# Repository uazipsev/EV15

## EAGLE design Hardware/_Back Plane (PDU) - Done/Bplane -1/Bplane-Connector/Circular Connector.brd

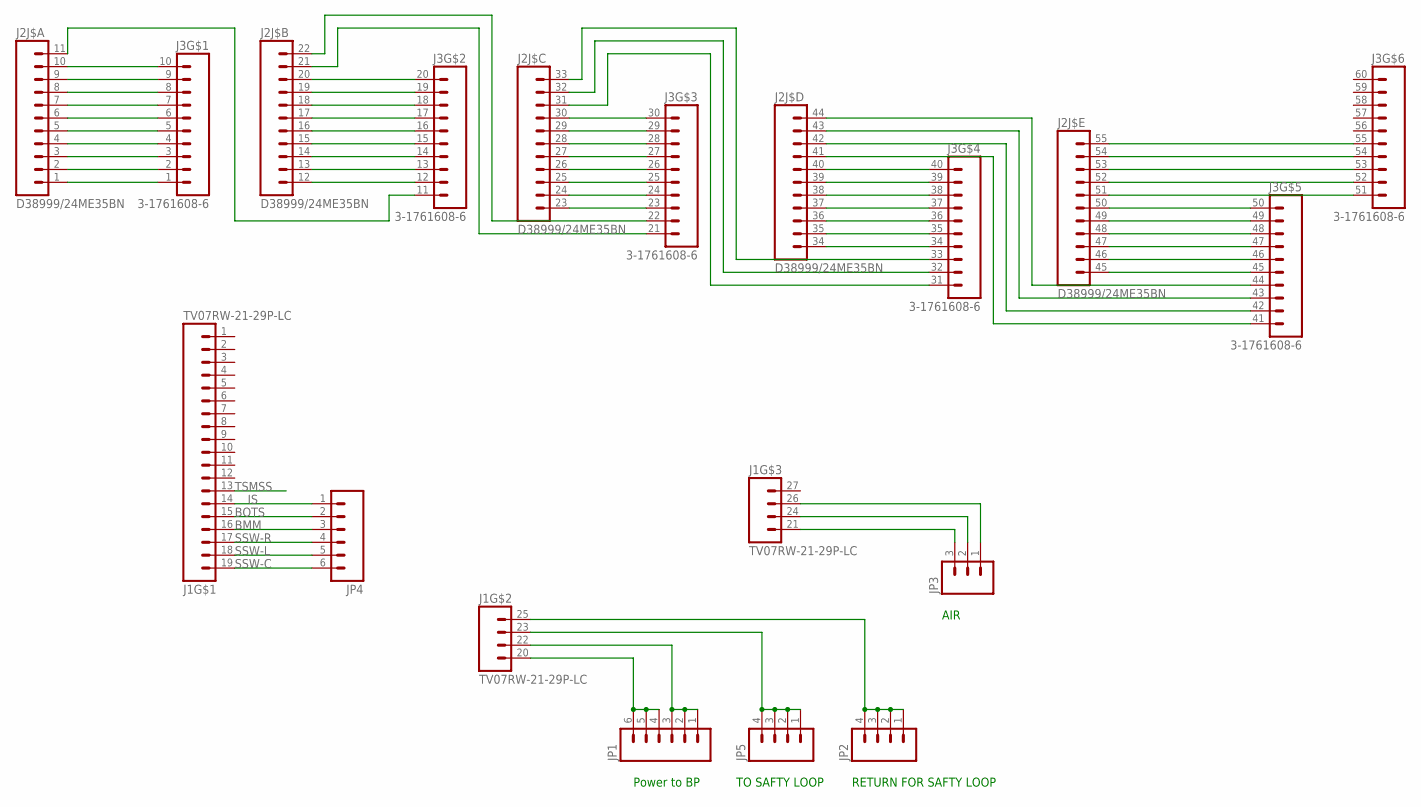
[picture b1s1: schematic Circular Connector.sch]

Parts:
J1: TV07RW-21-29P-LC
J2: D38999/24ME35BN
J3: 3-1761608-6
JP1, JP4: M06POLAR_LOCK; MOLEX-1X6_LOCK
JP2, JP5: M04POLAR_LOCK; MOLEX-1X4_LOCK
JP3: M03POLAR_LOCK; MOLEX-1X3_LOCK

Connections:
BMM: JP4.3
BOTS: JP4.2
IS: J1.14, JP4.1
unnamed: J2.1, J3.1
unnamed: J2.2, J3.2
unnamed: J2.3, J3.3
unnamed: J2.4, J3.4
unnamed: J2.5, J3.5
unnamed: J2.6, J3.6
unnamed: J2.7, J3.7
unnamed: J2.8, J3.8
unnamed: J2.9, J3.9
unnamed: J2.10, J3.10
unnamed: J2.11, J3.11 (1)
unnamed: J2.12 (1), J3.12 (2)
unnamed: J2.13 (2), J3.13 (3)
unnamed: J2.14 (3), J3.14 (4)
unnamed: J2.15 (4), J3.15 (5)
unnamed: J2.16 (5), J3.16 (6)
unnamed: J2.17 (6), J3.17 (7)
unnamed: J2.18 (7), J3.18 (8)
unnamed: J2.19 (8), J3.19 (9)
unnamed: J2.20 (9), J3.20 (10)
unnamed: J2.21 (10), J3.21 (1)
unnamed: J2.22 (11), J3.22 (2)
unnamed: J2.23 (1), J3.23 (3)
unnamed: J2.24 (2), J3.24 (4)
unnamed: J2.25 (3), J3.25 (5)
unnamed: J2.26 (4), J3.26 (6)
unnamed: J2.27 (5), J3.27 (7)
unnamed: J2.28 (6), J3.28 (8)
unnamed: J2.29 (7), J3.29 (9)
unnamed: J2.30 (8), J3.30 (10)
unnamed: J2.31 (9), J3.31 (1)
unnamed: J2.32 (10), J3.32 (2)
unnamed: J2.33 (11), J3.33 (3)
unnamed: J2.34 (1), J3.34 (4)
unnamed: J2.35 (2), J3.35 (5)
unnamed: J2.36 (3), J3.36 (6)
unnamed: J2.37 (4), J3.37 (7)
unnamed: J2.38 (5), J3.38 (8)
unnamed: J2.39 (6), J3.39 (9)
unnamed: J2.40 (7), J3.40 (10)
unnamed: J2.41 (8), J3.41 (1)
unnamed: J2.42 (9), J3.42 (2)
unnamed: J2.43 (10), J3.43 (3)
unnamed: J2.44 (11), J3.44 (4)
unnamed: J2.45 (1), J3.45 (5)
unnamed: J2.46 (2), J3.46 (6)
unnamed: J2.47 (3), J3.47 (7)
unnamed: J2.48 (4), J3.48 (8)
unnamed: J2.49 (5), J3.49 (9)
unnamed: J2.50 (6), J3.50 (10)
unnamed: J2.51 (7), J3.51 (1)
unnamed: J2.52 (8), J3.52 (2)
unnamed: J2.53 (9), J3.53 (3)
unnamed: J2.54 (10), J3.54 (4)
unnamed: J2.55 (11), J3.55 (5)
unnamed: J1.20 (1), JP1.4, JP1.5, JP1.6
unnamed: J1.22 (2), JP1.1, JP1.2, JP1.3
unnamed: J1.25 (4), JP2.1, JP2.2, JP2.3, JP2.4
unnamed: J1.21 (1), JP3.3
unnamed: J1.24 (2), JP3.2
unnamed: J1.26 (3), JP3.1
unnamed: J1.23 (3), JP5.1, JP5.2, JP5.3, JP5.4
SSW-C: J1.19, JP4.6
SSW-L: JP4.5
SSW-R: JP4.4
TSMSS: J1.13

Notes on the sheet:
Power to BP
RETURN FOR SAFTY LOOP
AIR
TO SAFTY LOOP

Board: 2 copper layers, 8 parts (3 on the bottom side), 64 nets, no tracks yet.

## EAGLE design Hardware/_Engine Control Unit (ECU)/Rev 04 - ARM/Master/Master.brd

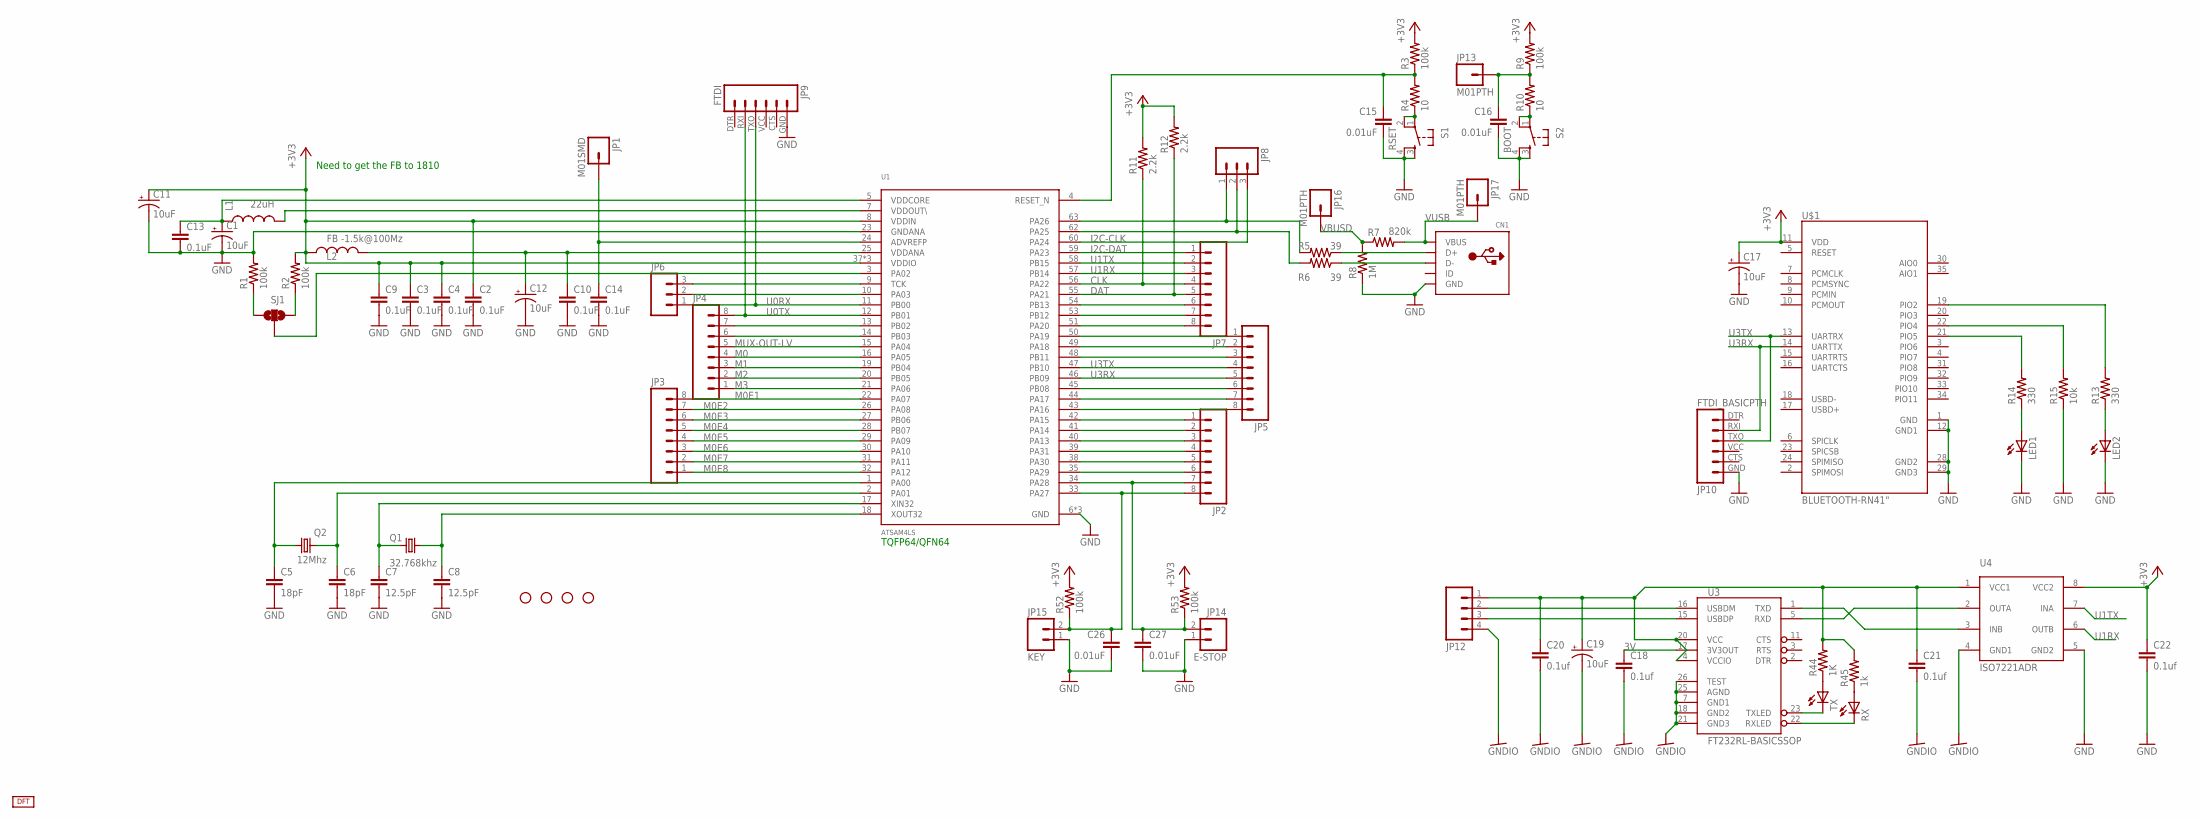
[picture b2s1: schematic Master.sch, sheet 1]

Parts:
C1, C11, C12, C17, C19: 10uF; EIA3216
C2, C3, C4, C9, C10, C13, C14: 0.1uF; 0805
C5, C6: 18pF; 0805
C7, C8: 12.5pF; 0805
C15, C16, C26, C27: 0.01uF; 0805
C18, C20, C21, C22: 0.1uf; 0805
CN1: USBMOLEX; USB-MINIB-THM-MOLEX
JP1: M01SMD; LUXEON-PAD
JP2, JP3, JP4, JP5, JP7: M08LOCK; 1X08_LOCK
JP6, JP8: M03LOCK; 1X03_LOCK
JP9: FTDI; FTDI_BASIC
JP10: FTDI_BASICPTH; FTDI_BASIC
JP12: M04POLAR_LOCK; MOLEX-1X4_LOCK
JP13, JP16, JP17: M01PTH; 1X01
JP14: E-STOP; 1X02_LOCK
JP15: KEY; 1X02_LOCK
L1: 22uH; 0805
L2: FB -1.5k@100Mz; 0805
LED1, LED2: LEDCHIP-LED0805; CHIP-LED0805
Q1: 32.768khz; MM20SS
Q2: 12Mhz; CTS406
R1, R2, R3, R9, R52, R53: 100k; 0805
R4, R10: 10; 0805
R5, R6: 39; 0805
R7: 820k; 0805
R8: 1M; 0805
R11, R12: 2.2k; 0805
R13, R14: 330; 0805
R15: 10k; 0805
R44: 1K; R0805
R45: 1k; R0805
RX: LEDCHIPLED_0805; CHIPLED_0805
S1: RSET; TACTILE-PTH
S2: BOOT; TACTILE-PTH
SJ1: SOLDERJUMPER_2WAYS; SJ_3
STANDOFF1, STANDOFF2, STANDOFF3, STANDOFF4: STAND-OFF
TX: LEDCHIPLED_0805; CHIPLED_0805
U1: ATSAM4LS; TQFP-64
U3: FT232RL-BASICSSOP; SSOP28DB
U4: ISO7221ADR; SOIC-8
U$1: BLUETOOTH-RN41"; RN41
U$12: LOGO; LOGO-S

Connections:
3V: C18.1, U3.17 (3V3OUT)
+3V3: C2.1, C3.1, C4.1, C9.1, C11.A (+), C17.A (+), C22.1, L2.1, R2.2, R3.2, R9.2, R11.2, R12.2, R52.2, R53.2, U1.8 (VDDIN), U1.37 (VDDIO), U1.52 (VDDIO), U1.61 (VDDIO), U4.8 (VCC2), U$1.11 (VDD); also elsewhere on the board
CLK: JP7.4, R11.1, U1.56 (PA22)
DAT: JP7.5, R12.1, U1.55 (PA21)
GND: C1.C (-), C2.2, C3.2, C4.2, C5.2, C6.2, C7.2, C8.2, C9.2, C10.2, C11.C (-), C12.C (-), C13.2, C14.2, C15.2, C16.2, C17.C (-), C22.2, C26.2, C27.2, CN1.GND, JP9.GND (6), JP10.GND (6), JP14.1, JP15.1, LED1.C, LED2.C, R1.2, R8.1, R15.1, S1.3, S1.4, S2.3, S2.4, U1.6 (GND), U1.23 (GNDANA), U1.36 (GND), U1.64 (GND), U4.5 (GND2), U$1.1 (GND), U$1.12 (GND1), U$1.28 (GND2), U$1.29 (GND3); also elsewhere on the board
GNDIO: C18.2, C19.C (-), C20.2, C21.2, JP12.4, U3.7 (GND1), U3.18 (GND2), U3.21 (GND3), U3.25 (AGND), U3.26 (TEST), U4.4 (GND1)
I2C-CLK: JP8.3, U1.60 (PA24); also elsewhere on the board
I2C-DAT: JP7.1, U1.59 (PA23); also elsewhere on the board
M0: JP4.4, U1.16 (PA05); also elsewhere on the board
M0E1: JP3.8, U1.22 (PA07); also elsewhere on the board
M0E2: JP3.7, U1.26 (PA08); also elsewhere on the board
M0E3: JP3.6, U1.27 (PB06); also elsewhere on the board
M0E4: JP3.5, U1.28 (PB07); also elsewhere on the board
M0E5: JP3.4, U1.29 (PA09); also elsewhere on the board
M0E6: JP3.3, U1.30 (PA10); also elsewhere on the board
M0E7: JP3.2, U1.31 (PA11); also elsewhere on the board
M0E8: JP3.1, U1.32 (PA12); also elsewhere on the board
M1: JP4.3, U1.19 (PB04); also elsewhere on the board
M2: JP4.2, U1.20 (PB05); also elsewhere on the board
M3: JP4.1, U1.21 (PA06); also elsewhere on the board
MUX-OUT-LV: JP4.5, U1.15 (PA04); also elsewhere on the board
unnamed: R4.1, S1.1, S1.2
unnamed: L1.2, U1.7 (VDDOUT\)
unnamed: C1.A (+), C13.1, L1.1, U1.5 (VDDCORE)
unnamed: C7.1, Q1.1, U1.17 (XIN32)
unnamed: SJ1.2, U1.3 (PA02)
unnamed: C8.1, Q1.4 (2), U1.18 (XOUT32)
unnamed: R1.1, SJ1.3
unnamed: C6.1, Q2.1, U1.2 (PA01)
unnamed: C5.1, Q2.3 (2), U1.1 (PA00)
unnamed: R2.1, SJ1.1
unnamed: C10.1, C12.A (+), L2.2, U1.25 (VDDANA)
unnamed: C14.1, JP1.P$1, U1.24 (ADVREFP)
unnamed: C15.1, R3.1, R4.2, U1.4 (RESET_N)
unnamed: R10.1, S2.1, S2.2
unnamed: CN1.D+, R5.1
unnamed: CN1.D-, R6.1
unnamed: C16.1, JP13.1, R9.1, R10.2
unnamed: JP8.1, R5.2, U1.63 (PA26)
unnamed: JP8.2, R6.2, U1.62 (PA25)
unnamed: LED2.A, R13.1
unnamed: JP2.1, U1.42 (PA15)
unnamed: JP2.2, U1.41 (PA14)
unnamed: JP2.3, U1.40 (PA13)
unnamed: JP2.4, U1.39 (PA31)
unnamed: JP2.5, U1.38 (PA30)
unnamed: JP2.6, U1.35 (PA29)
unnamed: C26.1, JP2.8, JP15.2, R52.1, U1.33 (PA27)
unnamed: C27.1, JP2.7, JP14.2, R53.1, U1.34 (PA28)
unnamed: C19.A (+), C20.1, C21.1, JP12.1, R44.2, R45.2, U3.4 (VCCIO), U3.20 (VCC), U4.1 (VCC1)
unnamed: JP12.2, U3.16 (USBDM)
unnamed: JP12.3, U3.15 (USBDP)
unnamed: R44.1, TX.A
unnamed: JP4.6, U1.14 (PB03)
unnamed: JP4.7, U1.13 (PB02)
unnamed: JP5.8, U1.43 (PA16)
unnamed: JP5.7, U1.44 (PA17)
unnamed: JP5.6, U1.45 (PB08)
unnamed: JP5.3, U1.48 (PB11)
unnamed: JP5.2, U1.49 (PA18)
unnamed: JP5.1, U1.50 (PA19)
unnamed: JP6.2, U1.10 (PA03)
unnamed: JP6.3, U1.9 (TCK)
unnamed: JP7.8, U1.51 (PA20)
unnamed: JP7.7, U1.53 (PB12)
unnamed: JP7.6, U1.54 (PB13)
unnamed: LED1.A, R14.1
unnamed: R14.2, U$1.21 (PIO5)
unnamed: R13.2, U$1.19 (PIO2)
unnamed: R45.1, RX.A
unnamed: R15.2, U$1.22 (PIO4)
unnamed: TX.C, U3.23 (TXLED)
unnamed: RX.C, U3.22 (RXLED)
unnamed: U3.1 (TXD), U4.3 (INB)
unnamed: U3.5 (RXD), U4.2 (OUTA)
U0RX: JP6.1, JP9.TXO (3), U1.11 (PB00)
U0TX: JP4.8, JP9.RXI (2), U1.12 (PB01)
U1RX: JP7.3, U1.57 (PB14), U4.6 (OUTB)
U1TX: JP7.2, U1.58 (PB15), U4.7 (INA)
U3RX: JP5.5, JP10.RXI (2), U1.46 (PB09), U$1.14 (UARTTX)
U3TX: JP5.4, JP10.TXO (3), U1.47 (PB10), U$1.13 (UARTRX)
VBUSD: JP16.1, R7.1, R8.2
VUSB: CN1.VBUS, JP17.1, R7.2

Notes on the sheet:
TQFP64/QFN64
Need to get the FB to 1810

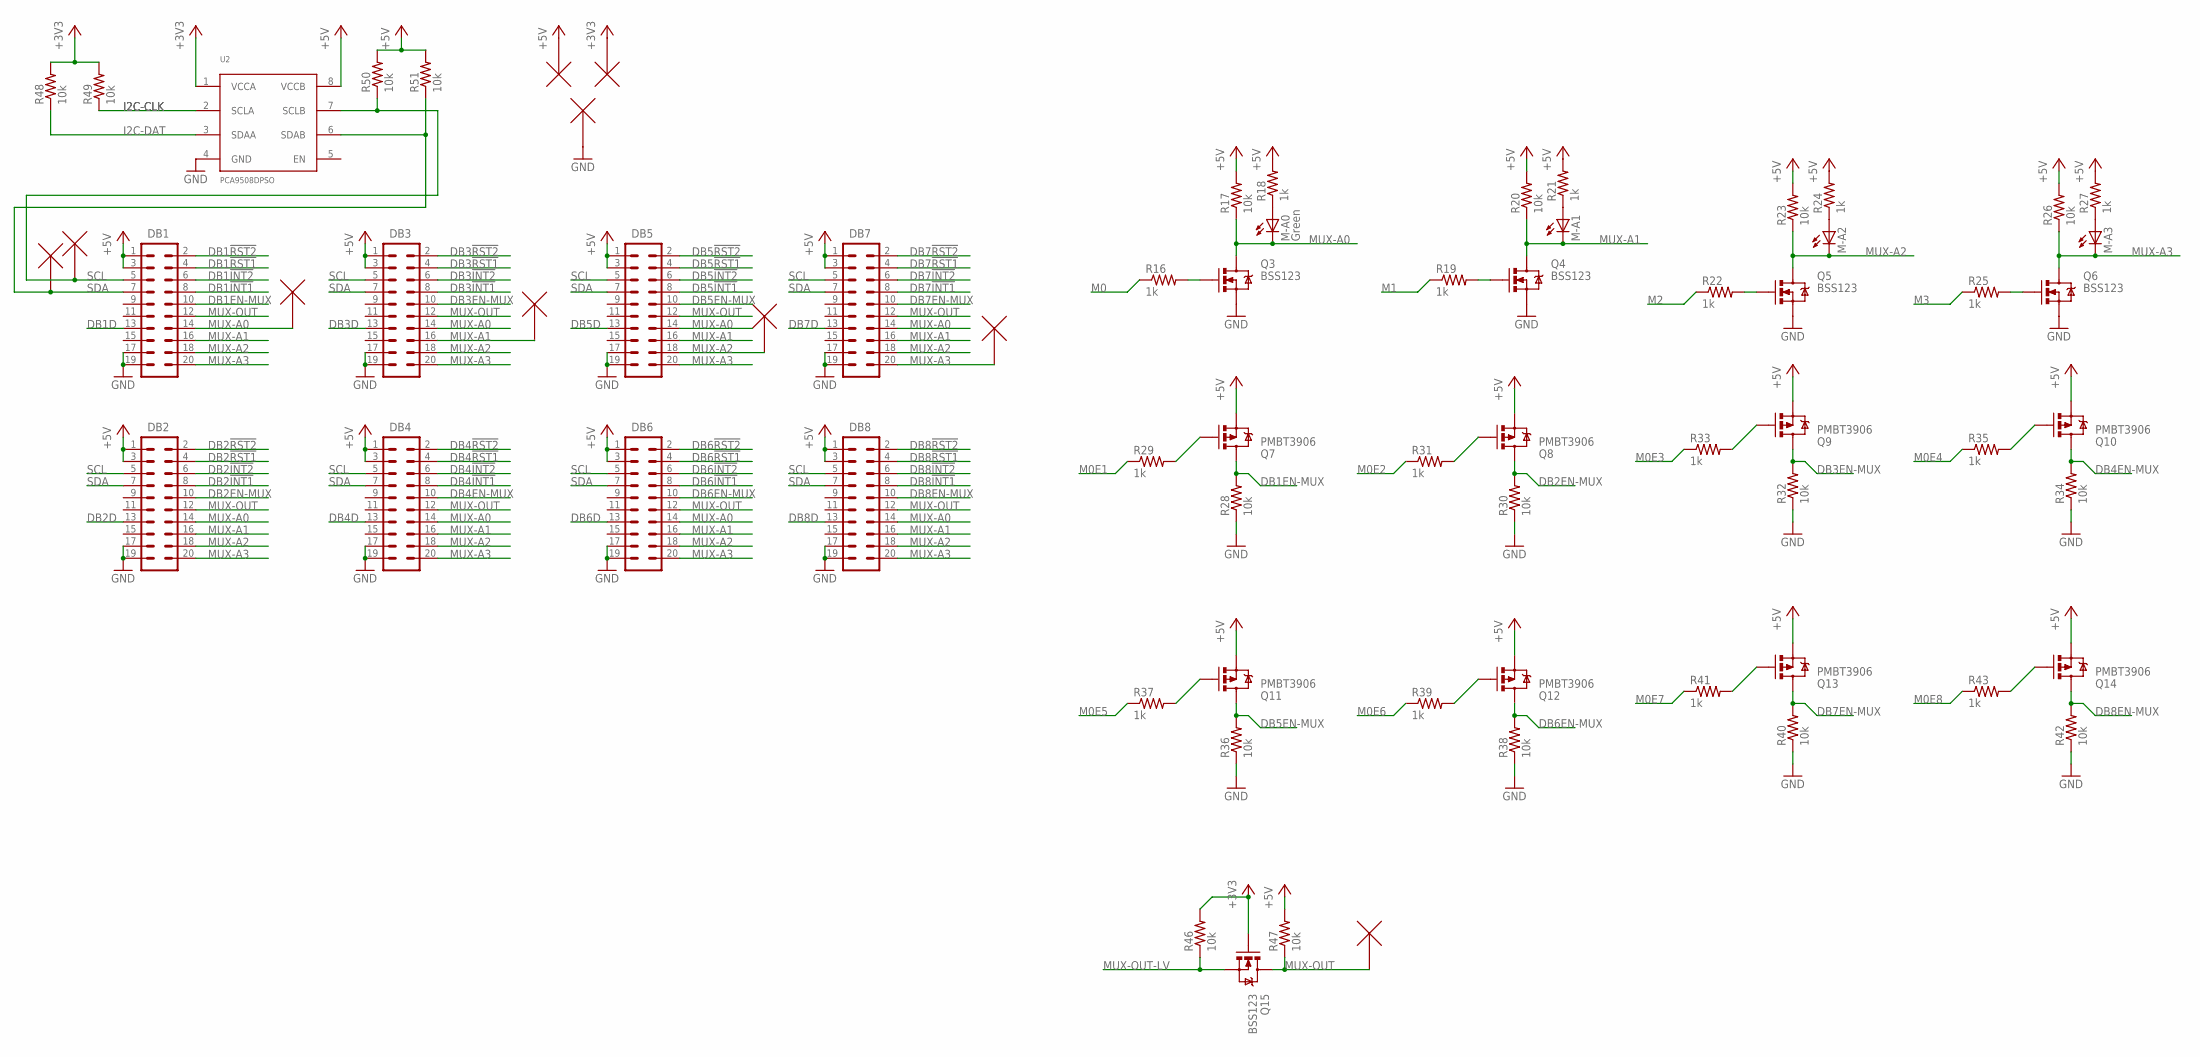
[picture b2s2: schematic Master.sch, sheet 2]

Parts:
DB1, DB2, DB3, DB4, DB5, DB6, DB7, DB8: M10X2SPECIAL; 2X10_LOCK_SPECIAL
M-A0: Green; CHIP-LED0805
M-A1, M-A2, M-A3: LEDCHIP-LED0805; CHIP-LED0805
Q3, Q4, Q5, Q6, Q15: BSS123; SOT23
Q7, Q8, Q9, Q10, Q11, Q12, Q13, Q14: PMBT3906; SOT23-3
R16, R18, R19, R21, R22, R24, R25, R27, R29, R31, R33, R35, R37, R39, R41, R43: 1k; 0805
R17, R20, R23, R26, R28, R30, R32, R34, R36, R38, R40, R42, R46, R47, R48, R49, R50, R51: 10k; 0805
U2: PCA9508DPSO; SO-8
U$2, U$3, U$4, U$5, U$6, U$7, U$8, U$9, U$10, U$13: TESTPOINT; R0603

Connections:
+3V3: Q15.1 (G), R46.2, R48.2, R49.2, U2.1 (VCCA), U$9.1, U$9.2; also elsewhere on the board
+5V: DB1.1, DB1.3, DB2.1, DB2.3, DB3.1, DB3.3, DB4.1, DB4.3, DB5.1, DB5.3, DB6.1, DB6.3, DB7.1, DB7.3, DB8.1, DB8.3, Q7.2 (S), Q8.2 (S), Q9.2 (S), Q10.2 (S), Q11.2 (S), Q12.2 (S), Q13.2 (S), Q14.2 (S), R17.2, R18.2, R20.2, R21.2, R23.2, R24.2, R26.2, R27.2, R47.2, R50.2, R51.2, U2.8 (VCCB), U$8.1, U$8.2; also elsewhere on the board
DB1!INT1: DB1.8
DB1!INT2: DB1.6
DB1!RST1: DB1.4
DB1!RST2: DB1.2
DB1D: DB1.13
DB1EN-MUX: DB1.10, Q7.3 (D), R28.2
DB2!INT1: DB2.8
DB2!INT2: DB2.6
DB2!RST1: DB2.4
DB2!RST2: DB2.2
DB2D: DB2.13
DB2EN-MUX: DB2.10, Q8.3 (D), R30.2
DB3!INT1: DB3.8
DB3!INT2: DB3.6
DB3!RST1: DB3.4
DB3!RST2: DB3.2
DB3D: DB3.13
DB3EN-MUX: DB3.10, Q9.3 (D), R32.2
DB4!INT1: DB4.8
DB4!INT2: DB4.6
DB4!RST1: DB4.4
DB4!RST2: DB4.2
DB4D: DB4.13
DB4EN-MUX: DB4.10, Q10.3 (D), R34.2
DB5!INT1: DB5.8
DB5!INT2: DB5.6
DB5!RST1: DB5.4
DB5!RST2: DB5.2
DB5D: DB5.13
DB5EN-MUX: DB5.10, Q11.3 (D), R36.2
DB6!INT1: DB6.8
DB6!INT2: DB6.6
DB6!RST1: DB6.4
DB6!RST2: DB6.2
DB6D: DB6.13
DB6EN-MUX: DB6.10, Q12.3 (D), R38.2
DB7!INT1: DB7.8
DB7!INT2: DB7.6
DB7!RST1: DB7.4
DB7!RST2: DB7.2
DB7D: DB7.13
DB7EN-MUX: DB7.10, Q13.3 (D), R40.2
DB8!INT1: DB8.8
DB8!INT2: DB8.6
DB8!RST1: DB8.4
DB8!RST2: DB8.2
DB8D: DB8.13
DB8EN-MUX: DB8.10, Q14.3 (D), R42.2
GND: DB1.17, DB1.19, DB2.17, DB2.19, DB3.17, DB3.19, DB4.17, DB4.19, DB5.17, DB5.19, DB6.17, DB6.19, DB7.17, DB7.19, DB8.17, DB8.19, Q3.2 (S), Q4.2 (S), Q5.2 (S), Q6.2 (S), R28.1, R30.1, R32.1, R34.1, R36.1, R38.1, R40.1, R42.1, U2.4 (GND), U$10.1, U$10.2; also elsewhere on the board
I2C-CLK: R49.1, U2.2 (SCLA); also elsewhere on the board
I2C-DAT: R48.1, U2.3 (SDAA); also elsewhere on the board
M0: R16.1; also elsewhere on the board
M0E1: R29.1; also elsewhere on the board
M0E2: R31.1; also elsewhere on the board
M0E3: R33.1; also elsewhere on the board
M0E4: R35.1; also elsewhere on the board
M0E5: R37.1; also elsewhere on the board
M0E6: R39.1; also elsewhere on the board
M0E7: R41.1; also elsewhere on the board
M0E8: R43.1; also elsewhere on the board
M1: R19.1; also elsewhere on the board
M2: R22.1; also elsewhere on the board
M3: R25.1; also elsewhere on the board
MUX-A0: DB1.14, DB2.14, DB3.14, DB4.14, DB5.14, DB6.14, DB7.14, DB8.14, M-A0.C, Q3.3 (D), R17.1, U$4.1, U$4.2
MUX-A1: DB1.16, DB2.16, DB3.16, DB4.16, DB5.16, DB6.16, DB7.16, DB8.16, M-A1.C, Q4.3 (D), R20.1, U$5.1, U$5.2
MUX-A2: DB1.18, DB2.18, DB3.18, DB4.18, DB5.18, DB6.18, DB7.18, DB8.18, M-A2.C, Q5.3 (D), R23.1, U$6.1, U$6.2
MUX-A3: DB1.20, DB2.20, DB3.20, DB4.20, DB5.20, DB6.20, DB7.20, DB8.20, M-A3.C, Q6.3 (D), R26.1, U$7.1, U$7.2
MUX-OUT: DB1.12, DB2.12, DB3.12, DB4.12, DB5.12, DB6.12, DB7.12, DB8.12, Q15.3 (D), R47.1, U$13.1, U$13.2
MUX-OUT-LV: Q15.2 (S), R46.1; also elsewhere on the board
unnamed: Q3.1 (G), R16.2
unnamed: M-A0.A, R18.1
unnamed: Q4.1 (G), R19.2
unnamed: M-A1.A, R21.1
unnamed: Q5.1 (G), R22.2
unnamed: M-A2.A, R24.1
unnamed: Q6.1 (G), R25.2
unnamed: M-A3.A, R27.1
unnamed: Q8.1 (G), R31.2
unnamed: Q7.1 (G), R29.2
unnamed: Q9.1 (G), R33.2
unnamed: Q10.1 (G), R35.2
unnamed: Q11.1 (G), R37.2
unnamed: Q12.1 (G), R39.2
unnamed: Q13.1 (G), R41.2
unnamed: Q14.1 (G), R43.2
SCL: DB1.5, DB2.5, DB3.5, DB4.5, DB5.5, DB6.5, DB7.5, DB8.5, R50.1, U2.7 (SCLB), U$2.1, U$2.2
SDA: DB1.7, DB2.7, DB3.7, DB4.7, DB5.7, DB6.7, DB7.7, DB8.7, R51.1, U2.6 (SDAB), U$3.1, U$3.2

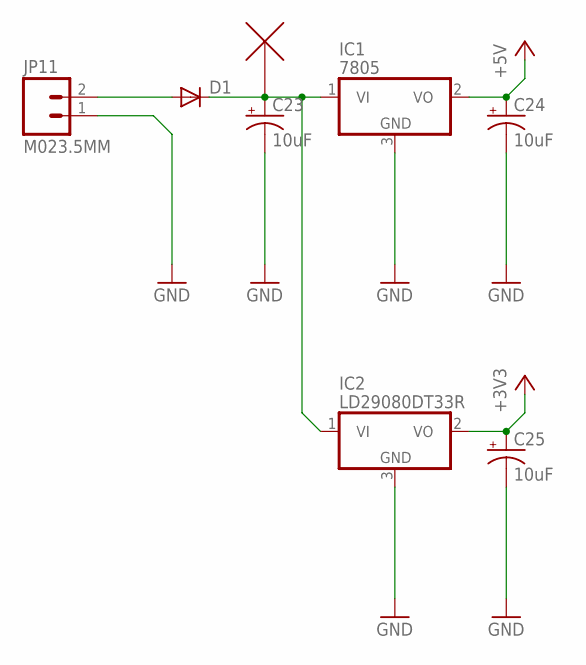
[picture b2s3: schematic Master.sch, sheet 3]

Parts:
C23: 10uF; EIA6032
C24, C25: 10uF; EIA3216
D1: DIODESMA; SMA-DIODE
IC1: 7805; TO252
IC2: LD29080DT33R; TO252
JP11: M023.5MM; SCREWTERMINAL-3.5MM-2
U$11: TESTPOINT; R0603

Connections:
+3V3: C25.A (+), IC2.2 (VO); also elsewhere on the board
+5V: C24.A (+), IC1.2 (VO); also elsewhere on the board
GND: C23.P$2 (-), C24.C (-), C25.C (-), IC1.3 (GND), IC2.3 (GND), JP11.1; also elsewhere on the board
unnamed: C23.P$1 (+), D1.C, IC1.1 (VI), IC2.1 (VI), U$11.1, U$11.2
unnamed: D1.A, JP11.2

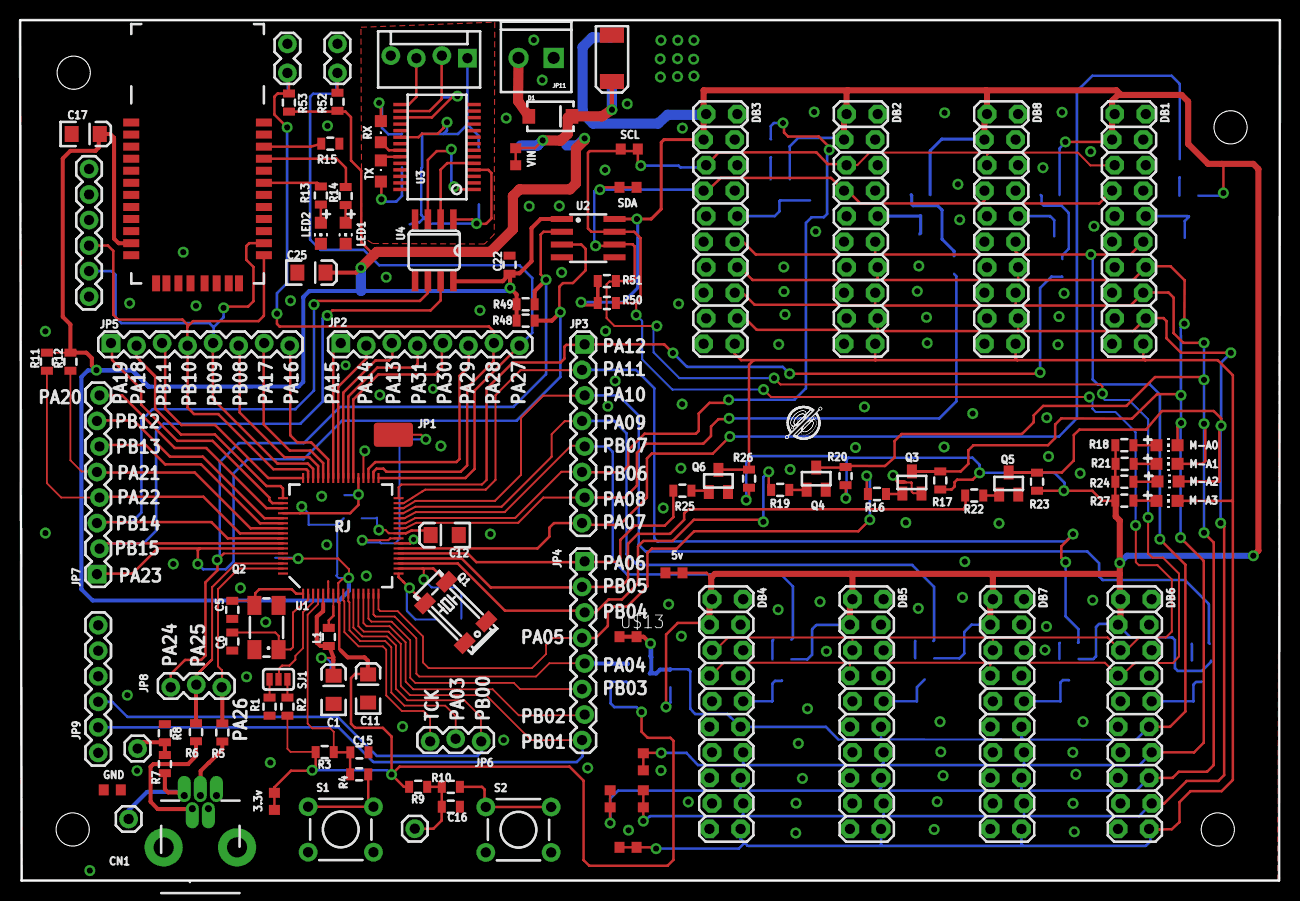
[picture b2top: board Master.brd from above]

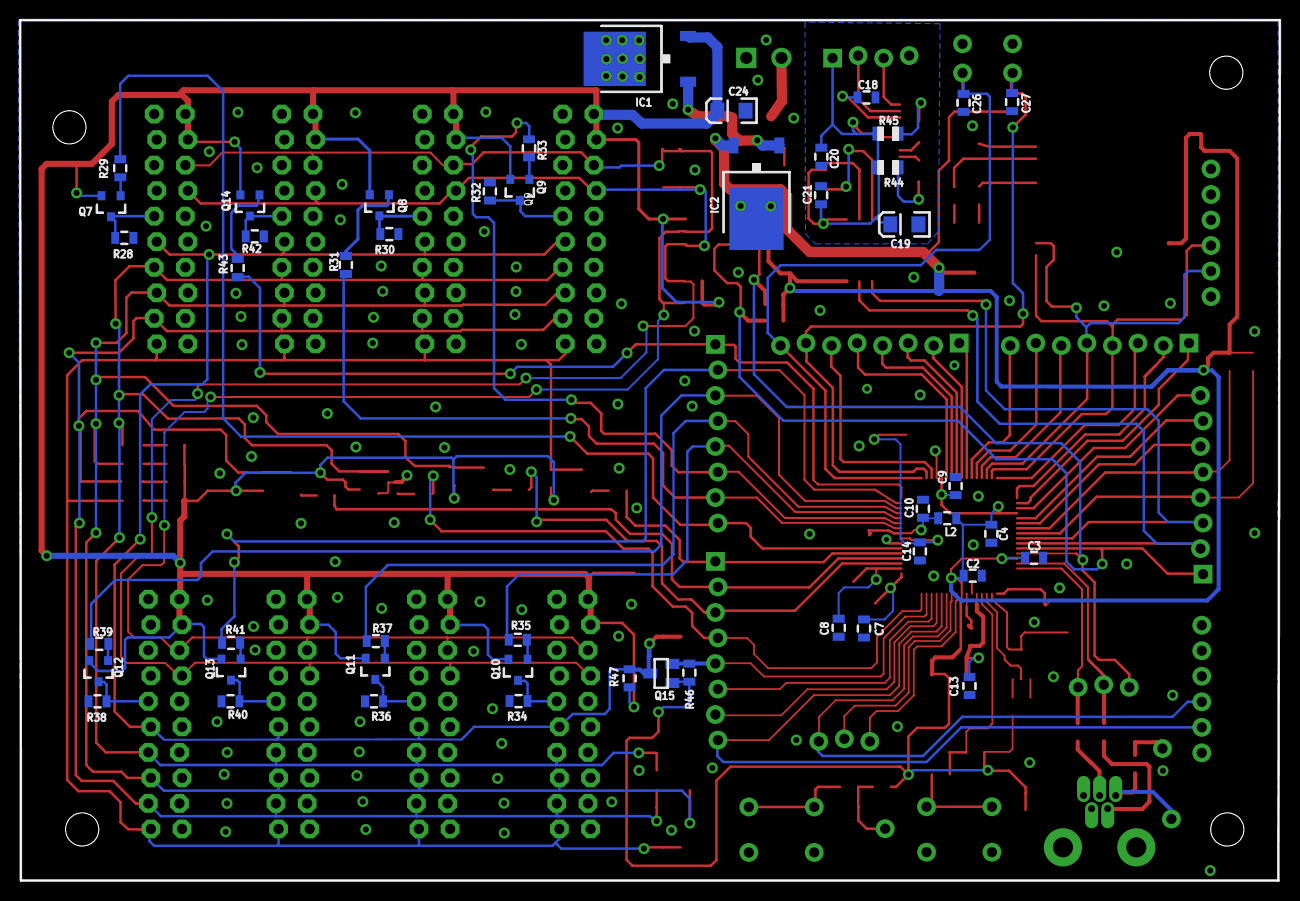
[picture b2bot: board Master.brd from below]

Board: 2 copper layers, 125.3 x 85.6 mm, 158 parts (48 on the bottom side), 117 nets.

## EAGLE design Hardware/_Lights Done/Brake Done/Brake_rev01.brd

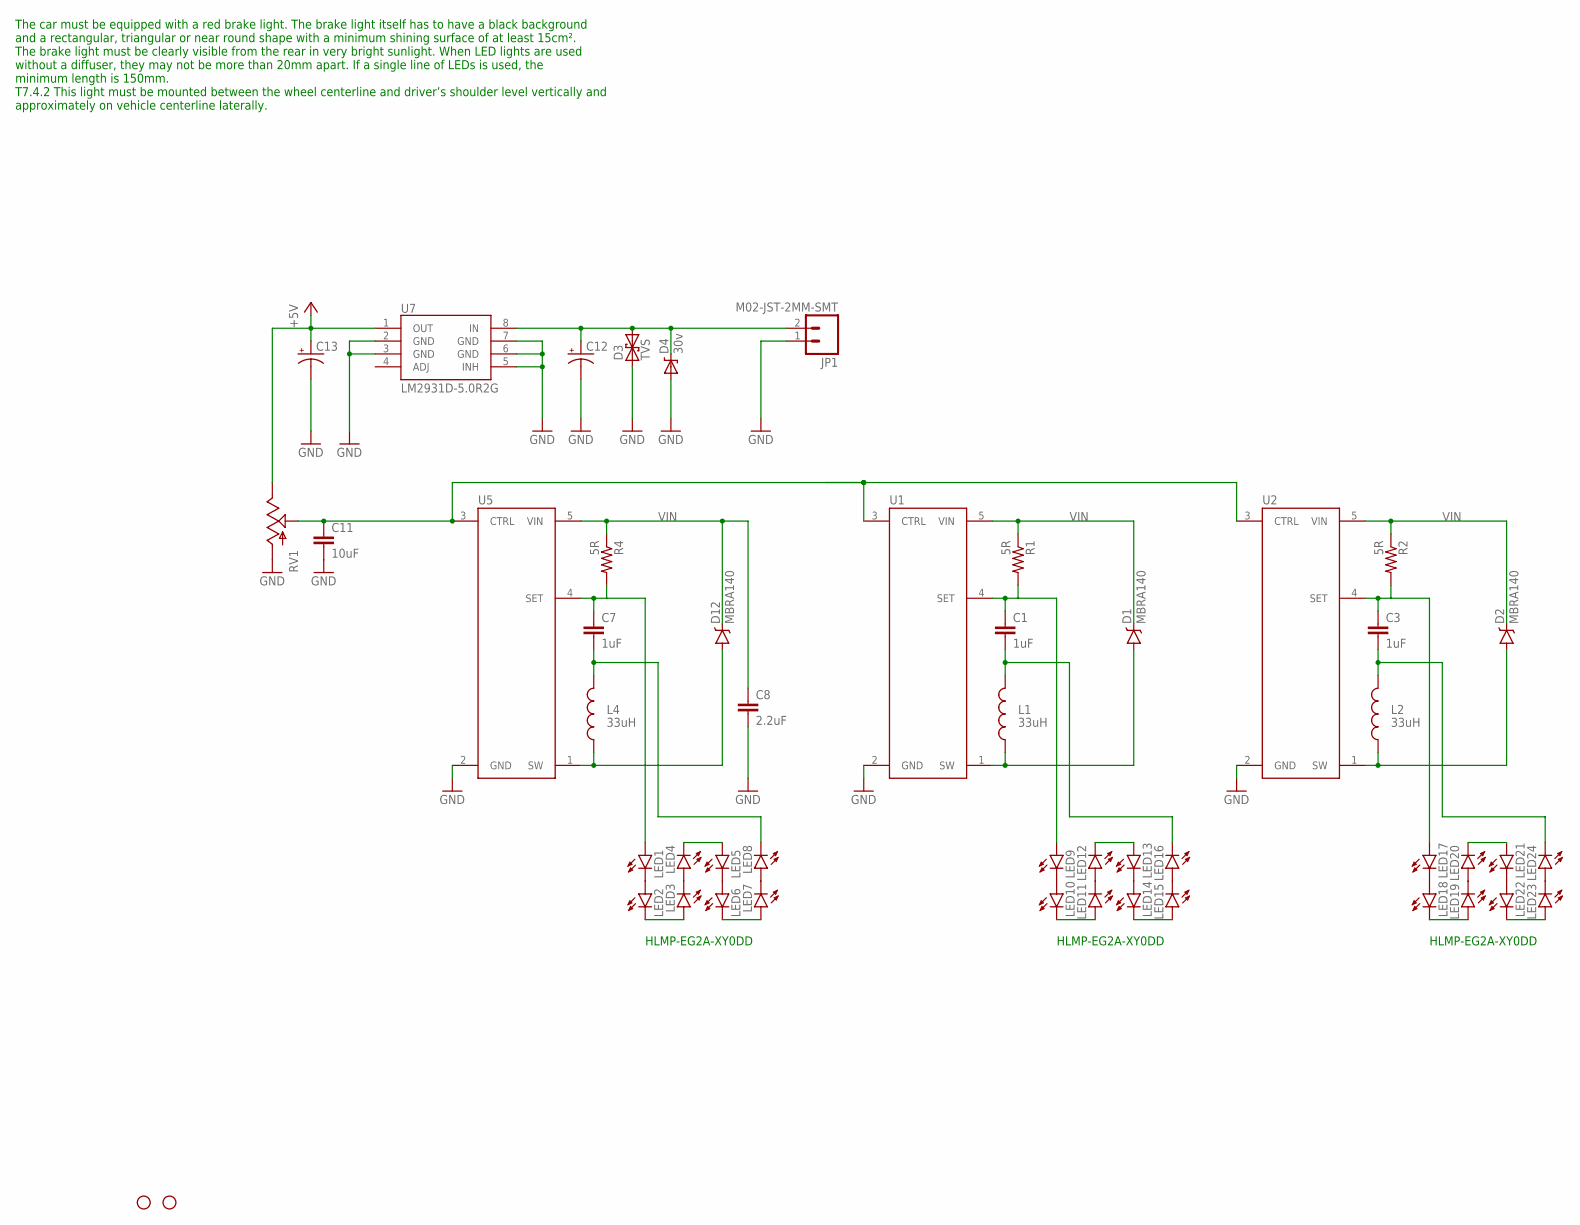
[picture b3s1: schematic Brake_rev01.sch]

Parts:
C1, C3, C7: 1uF; 1206
C8: 2.2uF; 1206
C11: 10uF; 0805
C12: CAP_POL6032; EIA6032
C13: CAP_POL1206; EIA3216
D1, D2, D12: MBRA140; SMA-DIODE
D3: TVS; SMA-DIODE
D4: 30v; SMB-DIODE
JP1: M02-JST-2MM-SMT; JST-2-SMD
L1, L2, L4: 33uH; SRN6045
LED1, LED2, LED3, LED4, LED5, LED6, LED7, LED8, LED9, LED10, LED11, LED12, LED13, LED14, LED15, LED16, LED17, LED18, LED19, LED20, LED21, LED22, LED23, LED24: LED5MM
R1, R2, R4: 5R; 0805
RV1: POTTRIM; TRIM_POT
STANDOFF1, STANDOFF2: STAND-OFF
U1, U2, U5: AL8805; SOT23-5
U7: LM2931D-5.0R2G; SO08

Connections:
+5V: C13.A (+), RV1.2 (E), U7.1 (OUT)
GND: C8.2, C11.2, C12.P$2 (-), C13.C (-), D3.A (1), D4.A, JP1.1 (2), RV1.3 (A), U1.2 (GND), U2.2 (GND), U5.2 (GND), U7.2 (GND), U7.3 (GND), U7.5 (INH), U7.6 (GND), U7.7 (GND)
unnamed: LED1.K (C), LED2.A
unnamed: LED3.K (C), LED4.A
unnamed: LED5.K (C), LED6.A
unnamed: LED7.K (C), LED8.A
unnamed: LED10.K (C), LED11.A
unnamed: LED12.K (C), LED13.A
unnamed: LED14.K (C), LED15.A
unnamed: LED9.K (C), LED10.A
unnamed: LED11.K (C), LED12.A
unnamed: LED13.K (C), LED14.A
unnamed: LED15.K (C), LED16.A
unnamed: LED18.K (C), LED19.A
unnamed: LED20.K (C), LED21.A
unnamed: LED22.K (C), LED23.A
unnamed: LED17.K (C), LED18.A
unnamed: LED19.K (C), LED20.A
unnamed: LED21.K (C), LED22.A
unnamed: LED23.K (C), LED24.A
unnamed: LED2.K (C), LED3.A
unnamed: LED4.K (C), LED5.A
unnamed: LED6.K (C), LED7.A
unnamed: C11.1, RV1.1 (S), U1.3 (CTRL), U2.3 (CTRL), U5.3 (CTRL)
OUT+1: C1.1, LED9.A, R1.2, U1.4 (SET)
OUT+2: C3.1, LED17.A, R2.2, U2.4 (SET)
OUT+3: C7.1, LED1.A, R4.2, U5.4 (SET)
OUT-1: C1.2, L1.2, LED16.K (C)
OUT-2: C3.2, L2.2, LED24.K (C)
OUT-3: C7.2, L4.2, LED8.K (C)
SW1: D1.A, L1.1, U1.1 (SW)
SW2: D2.A, L2.1, U2.1 (SW)
SW3: D12.A, L4.1, U5.1 (SW)
VIN: C8.1, C12.P$1 (+), D1.C, D2.C, D3.C (2), D4.C, D12.C, JP1.2 (1), R1.1, R2.1, R4.1, U1.5 (VIN), U2.5 (VIN), U5.5 (VIN), U7.8 (IN)

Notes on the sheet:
The car must be equipped with a red brake light. The brake light itself has to have a black background and a rectangular, triangular or near round shape with a minimum shining surface of at least 15cm². The brake light must be clearly visible from the rear in very bright sunlight. When LED lights a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
HLMP-EG2A-XY0DD

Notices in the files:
parts and their libraries:
SparkFun-Connectors: Licensing: CC v3.0 Share-Alike You are welcome to use this library for commercial purposes.
SparkFun-Passives: Licensing: Creative Commons ShareAlike 4.0 International - https://creativecommons.org/licenses/by-sa/4.0
